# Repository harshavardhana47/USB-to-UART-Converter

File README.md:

USB Type-C to UART Converter (CP2102)

Designed a USB Type-C to UART converter using the CP2102 in KiCad for reliable serial communication with embedded systems.

⚡ Integrated USB Type-C interface with proper CC configuration
🔄 Used CP2102 USB-to-UART bridge for TX/RX communication
🔧 Included decoupling capacitors and status LEDs for stability and debugging
📤 Exposed TX, RX, VBUS, GND pins for easy external interfacing
✅ ERC verified (0 errors) ensuring schematic reliability

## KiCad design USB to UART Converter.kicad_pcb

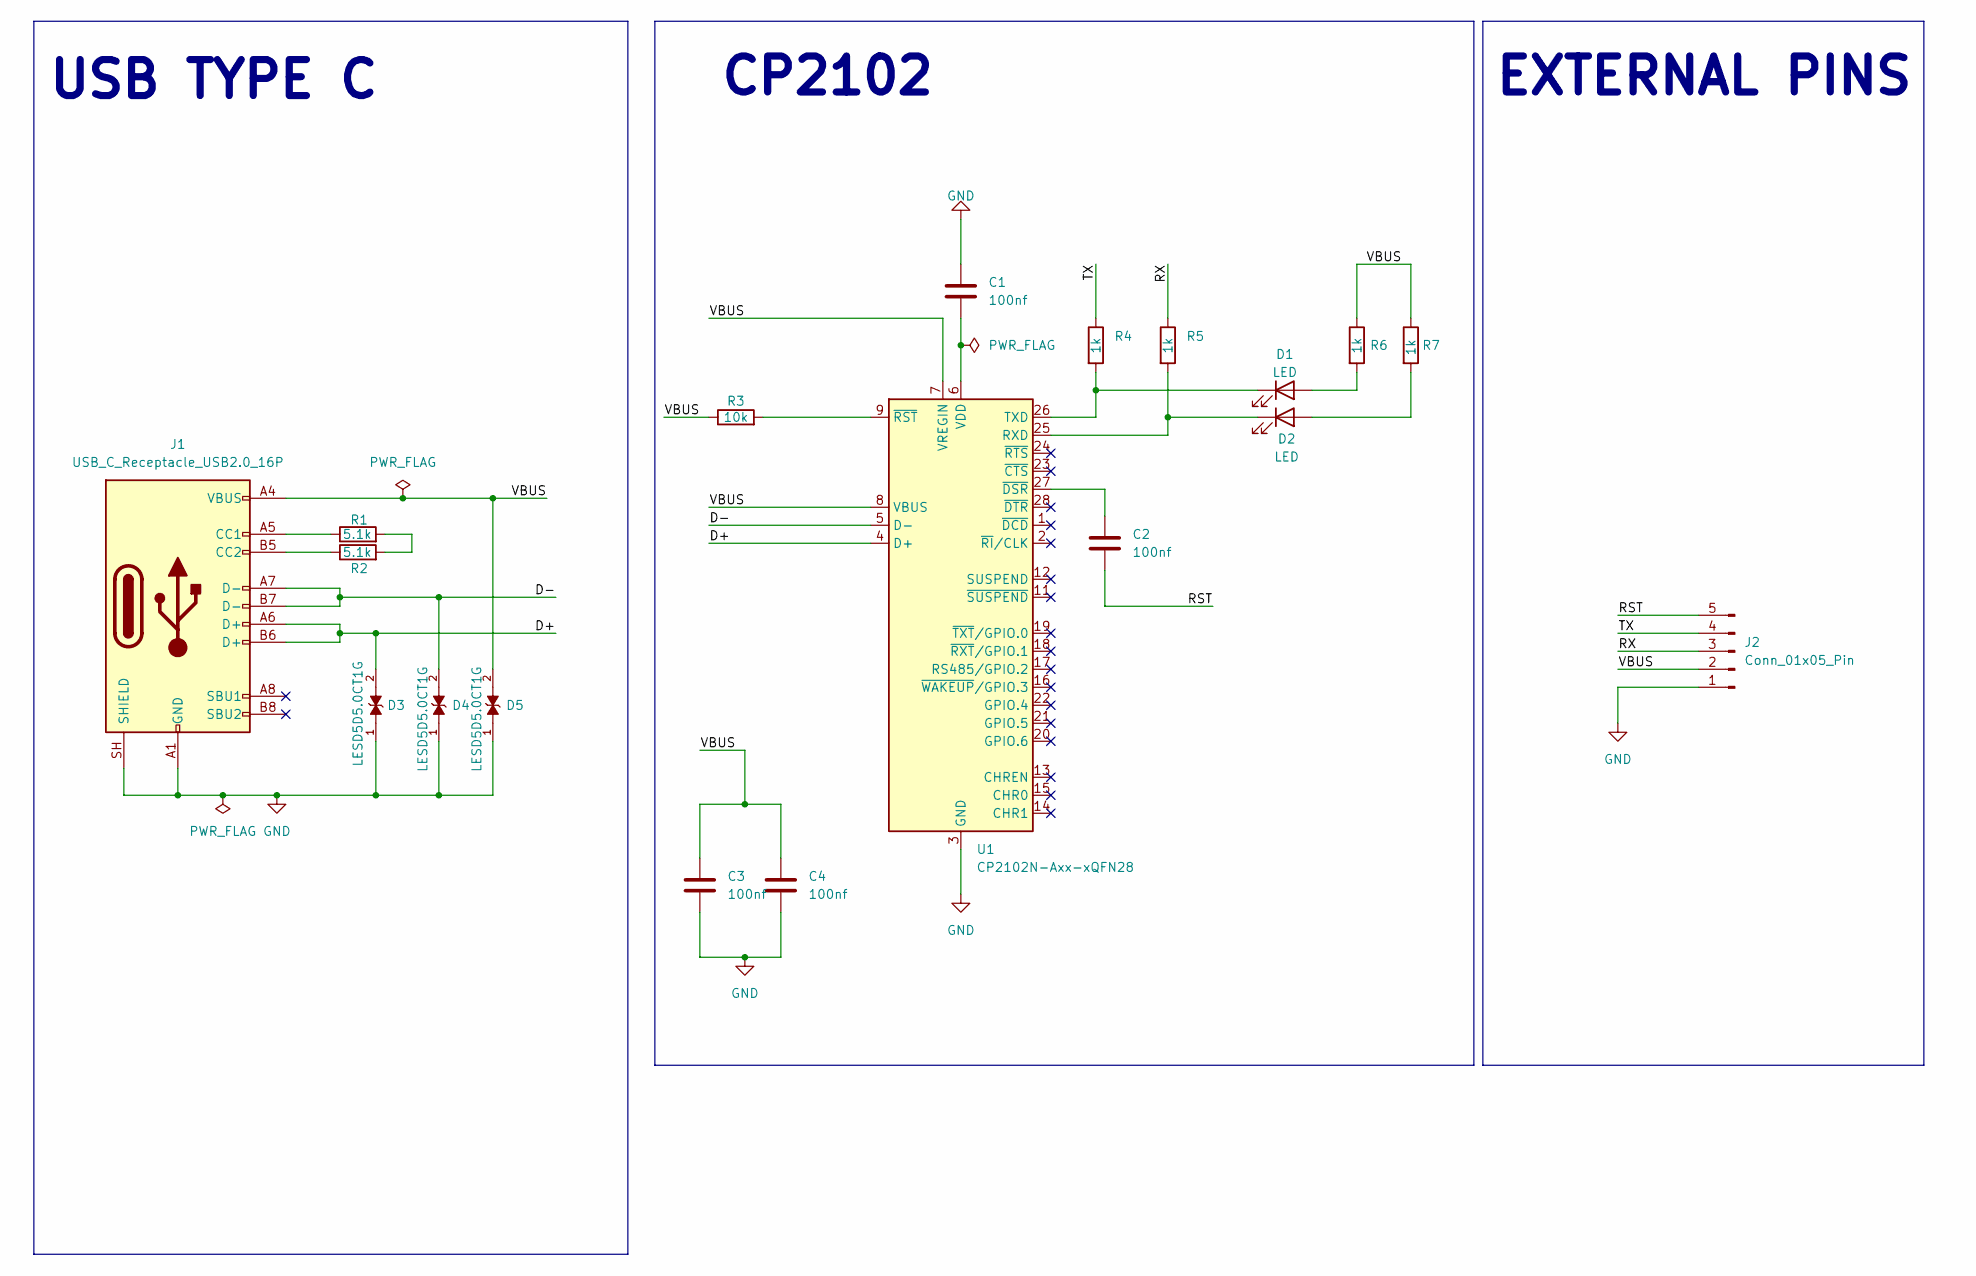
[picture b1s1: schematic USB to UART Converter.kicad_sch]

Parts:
C1, C2, C3, C4: 100nf; C_0402_1005Metric
D1, D2: LED; LED_0402_1005Metric
D3, D4, D5: LESD5D5.0CT1G; TVS_LESD5D5.0CT1G; PARTREV O
J1: USB_C_Receptacle_USB2.0_16P; USB_C_Receptacle_HRO_TYPE-C-31-M-12
J2: Conn_01x05_Pin; PinHeader_1x05_P2.54mm_Horizontal
R1, R2: 5.1k; R_0402_1005Metric
R3: 10k; R_0402_1005Metric
R4, R5, R6, R7: 1k; R_0402_1005Metric
U1: CP2102N-Axx-xQFN28; QFN-28-1EP_5x5mm_P0.5mm_EP3.35x3.35mm

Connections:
/D+: D3.2, J1.A6 (D+), J1.B6 (D+), U1.4 (D+)
/D-: D4.2, J1.A7 (D-), J1.B7 (D-), U1.5 (D-)
/RST: C2.2, J2.5
/RX: J2.3, R5.1
/TX: J2.4, R4.1
/VBUS: C3.1, C4.1, D5.2, J1.A4 (VBUS), J1.A9 (VBUS), J1.B4 (VBUS), J1.B9 (VBUS), J2.2, R3.1, R6.1, R7.1, U1.7 (VREGIN), U1.8 (VBUS)
GND: C1.1, C3.2, C4.2, D3.1, D4.1, D5.1, J1.A1 (GND), J1.A12 (GND), J1.B1 (GND), J1.B12 (GND), J1.SH (SHIELD), J2.1, U1.3 (GND), U1.29 (GND)
unnamed: D1.2 (A), R6.2
unnamed: D1.1 (K), R4.2, U1.26 (TXD)
unnamed: D2.2 (A), R7.2
unnamed: D2.1 (K), R5.2, U1.25 (RXD)
unnamed: J1.A5 (CC1), R1.1
unnamed: J1.B5 (CC2), R2.1
unnamed: R1.2, R2.2
unnamed: C1.2, U1.6 (VDD)
unnamed: C2.1, U1.27 (~DSR)
unnamed: R3.2, U1.9 (~RST)

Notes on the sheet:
USB TYPE C
EXTERNAL PINS
CP2102

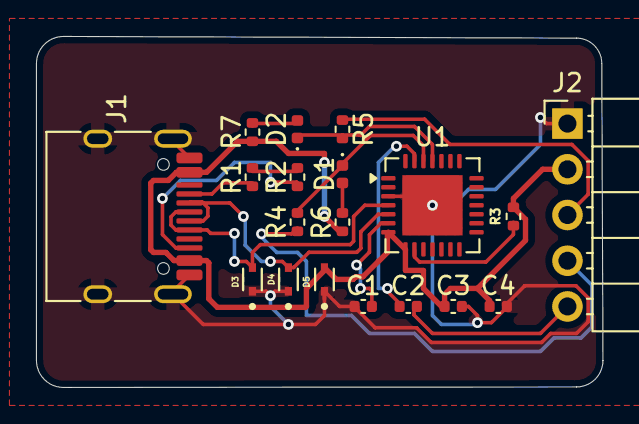
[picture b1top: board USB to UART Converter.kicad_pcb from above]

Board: 2 copper layers, 31.5 x 19.5 mm, 19 parts (0 on the bottom side), 17 nets.

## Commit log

2026-05-03 Add files via upload
    As you can see in "PCB Design & DRC Check.png" I'm not able to resolve those warning and I'm not able to understand how to solve them. Can anyone seeing this post let me know what does it mean and ho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
